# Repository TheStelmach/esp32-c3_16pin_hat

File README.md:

# esp32-c3_16pin_hat
ESP32-C3_16pin_devboard_hat

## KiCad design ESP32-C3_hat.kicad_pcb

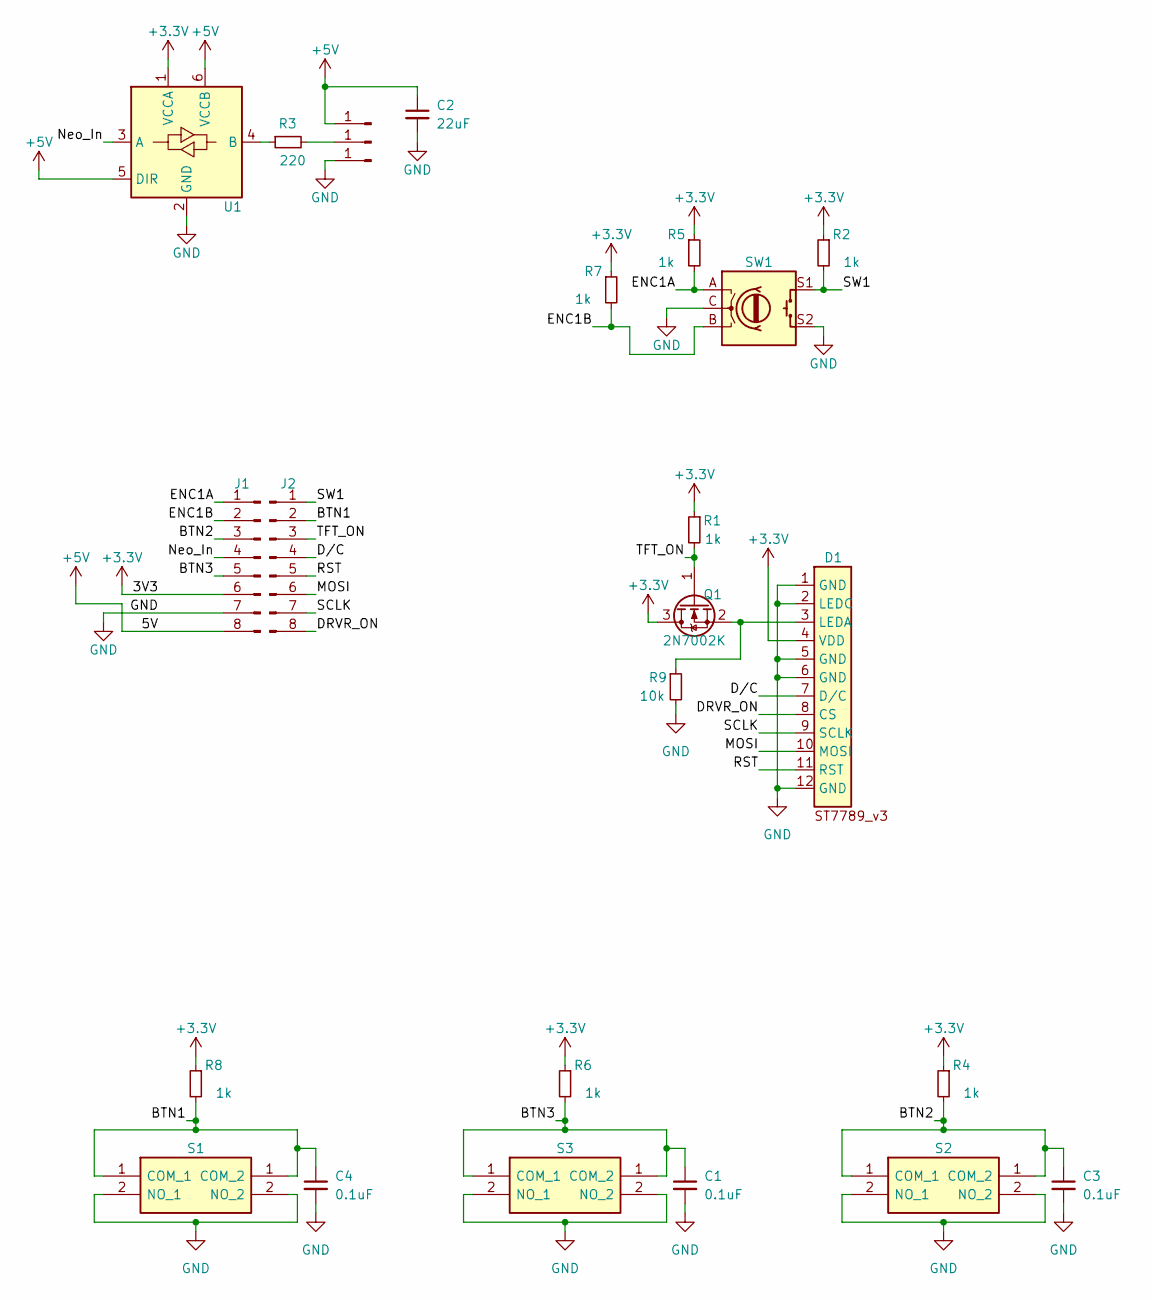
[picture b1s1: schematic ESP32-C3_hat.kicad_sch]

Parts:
C1, C3, C4: 0.1uF; C_1206_3216Metric_Pad1.33x1.80mm_HandSolder
C2: 22uF; C_0805_2012Metric_Pad1.18x1.45mm_HandSolder
D1: 12pin_SPI_Display_connector_ST7789
J1, J2: Conn_01x08_Pin; PinHeader_1x08_P2.54mm_Vertical
J3, J4, J5: Conn_01x01_Pin; TestPoint_Loop_D2.60mm_Drill1.6mm_Beaded
Q1: 2N7002K; SOT-23
R1, R2, R4, R5, R6, R7, R8: 1k; R_1206_3216Metric_Pad1.30x1.75mm_HandSolder
R3: 220; R_1206_3216Metric_Pad1.30x1.75mm_HandSolder
R9: 10k; R_1206_3216Metric_Pad1.30x1.75mm_HandSolder
S1, S2, S3: RKB2SJM250SMTR_LFS; SW_SPST_TL3342; Mouser Part Number 611-RKB2SJM250SMTRLF
SW1: RotaryEncoder_Switch; RotaryEncoder_Alps_EC11E-Switch_Vertical_H20mm
U1: SN74LVC1T45DCK; SOT-23-6_Handsoldering

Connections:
+3.3V: D1.4 (VDD), J1.6, Q1.3 (D), R1.1, R2.1, R4.1, R5.1, R6.1, R7.1, R8.1, U1.1 (VCCA)
+5V: C2.1, J1.8, J4.1, U1.5 (DIR), U1.6 (VCCB)
/BTN1: C4.1, J2.2, R8.2, S1.1 (COM_2)
/BTN2: C3.1, J1.3, R4.2, S2.1 (COM)
/BTN3: C1.1, J1.5, R6.2, S3.1 (COM_2)
/DRVR_ON: D1.8 (CS), J2.8
/D/C: D1.7 (D/C), J2.4
/ENC1A: J1.1, R5.2, SW1.A
/ENC1B: J1.2, R7.2, SW1.B
/MOSI: D1.10 (MOSI), J2.6
/Neo_In: J1.4, U1.3 (A)
/RST: D1.11 (RST), J2.5
/SCLK: D1.9 (SCLK), J2.7
/SW1: J2.1, R2.2, SW1.S1
/TFT_ON: J2.3, Q1.1 (G), R1.2
GND: C1.2, C2.2, C3.2, C4.2, D1.1 (GND), D1.2 (LEDC), D1.5 (GND), D1.6 (GND), D1.12 (GND), J1.7, J5.1, R9.2, S1.2 (NO_1), S2.2 (NO), S3.2 (NO_1), SW1.C, SW1.S2, U1.2 (GND)
unnamed: D1.3 (LEDA), Q1.2 (S), R9.1
unnamed: J3.1, R3.2
unnamed: R3.1, U1.4 (B)

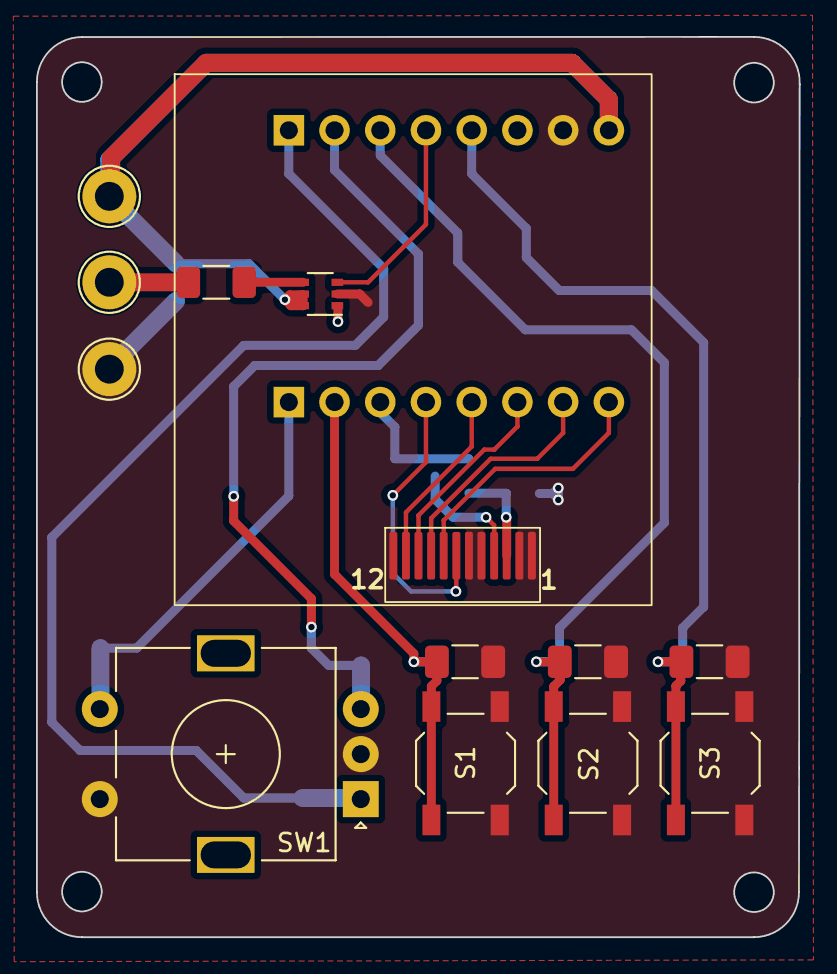
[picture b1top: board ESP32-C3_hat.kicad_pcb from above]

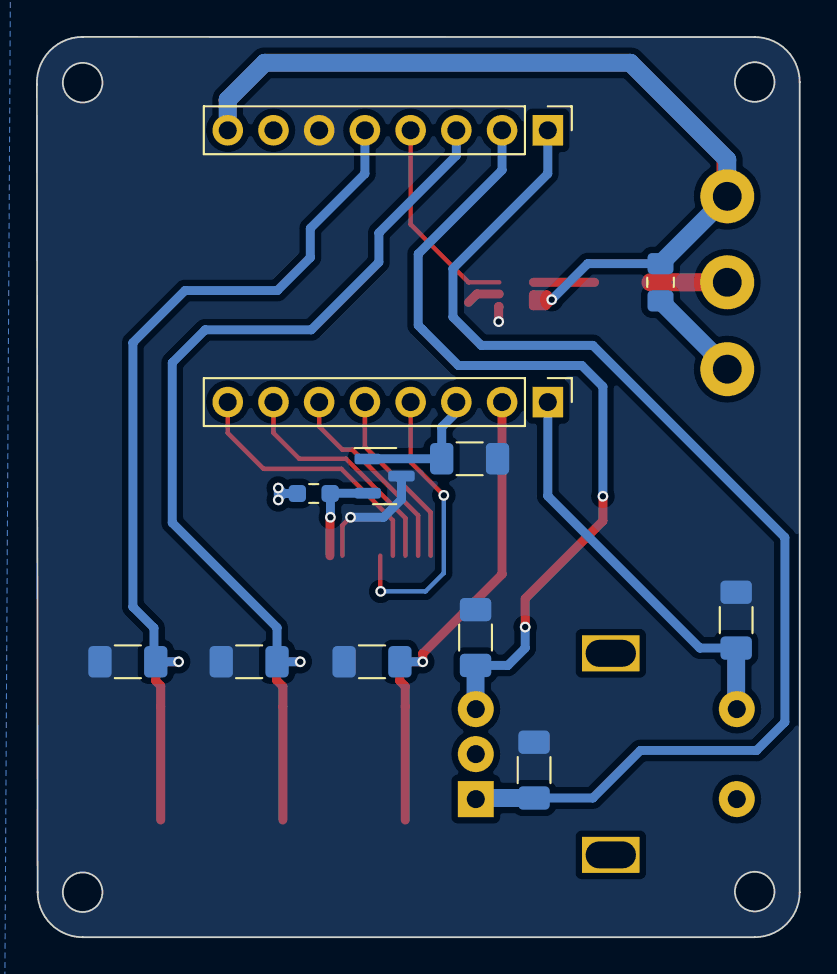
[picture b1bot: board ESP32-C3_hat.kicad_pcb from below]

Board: 2 copper layers, 42.4 x 50.0 mm, 25 parts (12 on the bottom side), 19 nets.

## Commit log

2024-01-11 Add files via upload
    Simple hat to route out the pinout from the ESP32-C3 16pin devboard to the following peripherals:
    -ST7789 1.3" display with SPI interface
    -Neopixel data pin, +5V & GND
    -Three tactile switches and one incremental encoder for user input.
    The neopixel data signal is translated back from 3.3V to 5V via a voltage shifter.
